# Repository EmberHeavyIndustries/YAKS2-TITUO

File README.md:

# YAKS2 - TITUO

**If you like this project and want to contribute to its further development, please consider donate some $ or € (paypal friends & family, please or DO NOT select "Buying something" from money transfer frontpage).** 

| |||
| ------------------------------ | ---------------------------------------------- | --------------------------- |

**YAKS2-TITUO** is an **"Intelligent" kickstart switcher** for the Amiga A500-A600-A2000 and A1200-A4000, with unique features:

- A500/A600/A2000 version
  - Can switch among four or eight different kickstarts
  - Kickstarts can be flashed at any time by mean of YAKS2 adapter and any common chip flasher, capable of managing 29F080 chips
  - Kickstart selection by mean of CTRL-A-A without the need of any additional wiring inside Amiga
  - Keep track of the selected kickstart upon poweroff
  - Optional audible kickstart selection confirmation 

- A1200/A4000 version
  - Can switch among two or four different kickstarts
  - Kickstarts must be flashed before board assembling (not re-flashable)
  - Kickstart selection by mean of CTRL-A-A without the need of any additional wiring inside Amiga
  - Keep track of the selected kickstart upon poweroff
  - Optional audible kickstart selection confirmation 

## YAKS2-TITUO FLAVORS

The kickswitcher comes in three differen flavors, according to intened use and user preferences:

### **YAKS2-TITUO R02.1**

- Suitable for A500, A600, A2000
- Kickstart images can be flashed at any time (by mean of YAKS2->29F080 adaptor)
- Firmware can be upgraded via ICSP
- Kickstart selection by CTRL-A-A and RST methods (can be easily modded for AUTOSENSE - 1 wire mod)
- Onboard buzzer for audible kickstart switch and named selection evidence
- "D" shaped footprint
- Can switch among 4-kickstart-images or 8-kickstart-images

### **YAKS2-TITUO R03.1al**

- Suitable for A500, A600, A2000
- Kickstart images can be flashed at any time (by mean of YAKS2->29F040 adaptor)
- Firmware cannot be upgraded via ICSP
- Kickstart selection by CTRL-A-A, support both AUTOSENSE (no additional wires) and RST methods
- Can connect an onboard buzzer for audible kickstart switch and named selection evidence
- Visible kickstart switch and named selection evidence
- Small footprint
- Can switch among 4-kickstart-images or 8-kickstart-images

### **YAKS2-TITUO R04.1bl**

- Suitable for A1200 and A4000
- Kickstart images cannot be re-flashed 
- Firmware CAN be upgraded via ICSP
- Kickstart selection by CTRL-A-A, support both AUTOSENSE (no additional wires) and RST methods
- Can connect an external buzzer for audible kickstart switch and named selection evidence
- Visible kickstart switch and named selection evidence
- Small footprint
- Can switch among 2-kickstart-images or 4-kickstart-images

/*************** EDITING IN PROGRESS *************************/

### **EAGLE SCHEMATICS, BOARD LAYOUT and GERBER FILES**

All schemtacis, layouts, gerber files and BOM are in 'Docs' subdirectory

### **FIRMWARE**

Preferred firmware can be downloaded from 'Firmware' subdirectory

## **LICENSE TERMS**

### **Schematics, pcb layouts,  gerbers **
of YAKS2-TITUO are open source, released under the Creative Commons CC BY-NC license.
This means that you are free to:

|                      |                                                                        |
| -------------------- | ---------------------------------------------------------------------- |
|      SHARE           |      copy and redistribute the material in any medium or format        |
|      ADAPT           |      remix, transform, and build upon the material                     |

Under the following terms:

|                       |                                                                        |
| --------------------- | ---------------------------------------------------------------------- |
|     Attribution       | You must give appropriate credit, provide a link to the license, and indicate if changes were made. You may do so in any reasonable manner, but not in any way that suggests the licensor endorses you or your use. |
|      NonCommercial    | You may not use the material for commercial purposes.                  |
|      ShareAlike       | If you remix, transform, or build upon the material, you must distribute your contributions under the same license as the original.          |
| No additional restrict| You may not apply legal terms or technological measures that legally restrict others from doing anything the license permits.  |

### **YAKS2-TITUO FIRMWARE** 
is free to download, copy and redistribuite to be used in conjuction with any YAKS2-TITUO board.
The firmware **CANNOT** be in any way:
- used for any other purpose than YAKS2-TITUO (e.g. flashed in other boards)
- sold, rent or leased. If you were asked to pay for it, you've been tricked

## **Warranty Disclaimer and Limitation of Liability**

YAKS2-TITUO is an hobbyist project without any commercial intention; you understand that we cannot and do not guarantee or warrant neither the YAKS2-TITUO hardware (including but not limited to: schematics, gerbers, pcb, components, assembling, etc.) nor the YAKS2-TITUO software (firmware, etc) from defects, breakage or loss of functionality. You are using HID2AMI under your exclusive risk and responsibility; please understand and AGREE that **WE WILL NOT BE LIABLE FOR ANY LOSS OR DAMAGE CAUSED BY EITHER ANY USE OR ANY MISUSE OF YAKS2-TITUO**

BY MAKING USE OF YAKS2-TITUO, YOU EXPRESSLY AGREE THAT YOUR WILL ACCEPT IT ON "AS IS" BASIS WITHOUT ANY WARRANTIES OF ANY KIND, EITHER EXPRESS OR IMPLIED. YOU ALSO EXPRESSELY AGREE THAT YOUR USE OF HID2AMI HARDWARE AND ITS SOFTWARE COMPONENTS IS AT YOUR OWN RISK. NEITHER THE AUTHOR (Sampedenawa) NOR ANY PERSON ASSOCIATED WITH THE AUTHOR MAKES ANY WARRANTY OR REPRESENTATION WITH RESPECT TO THE COMPLETENESS, SECURITY, RELIABILITY, QUALITY, ACCURACY OR AVAILABILITY OF THE HID2AMI HARDWARE/SOFTWARE.

IF YOU DO NOT UNDERSTAND AND EXPRESSLY AGREE WHAT STATED ABOVE, YOU ARE NOT ENTITLED BY THE AUTHOR TO USE HID2AMI FOR ANY PURPOSE.

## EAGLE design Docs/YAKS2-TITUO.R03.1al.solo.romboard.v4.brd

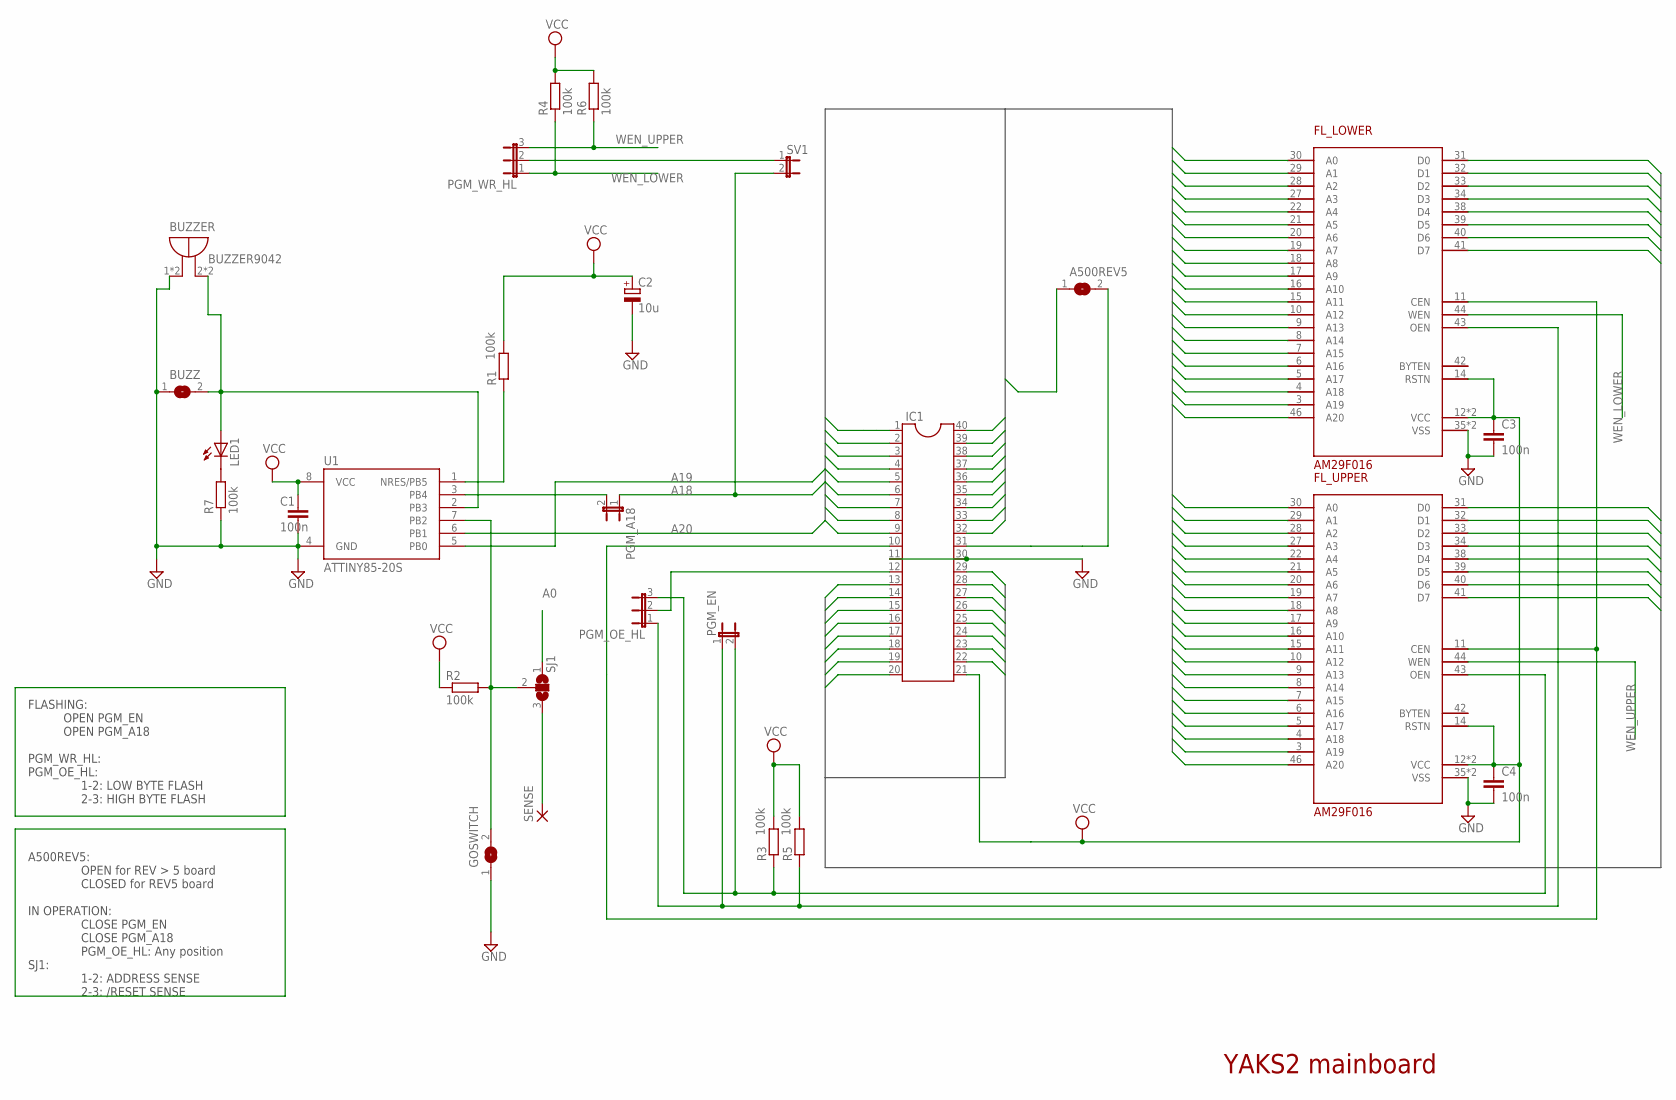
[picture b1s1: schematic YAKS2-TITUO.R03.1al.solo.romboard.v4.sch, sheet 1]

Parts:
A500REV5: SJ
BUZZ: SJ
BUZZER: BUZZER9042; CAPPRD400W65D900H420B
C1, C3, C4: 100n; C0805
C2: 10u; B/3528-21R
FL_LOWER: AM29F016; TSOP48
FL_UPPER: AM29F016; TSOP48
GOSWITCH: SJ
IC1: DIL40
LED1: LEDSML0805; SML0805
PGM_A18: JP1E; JP1
PGM_EN: JP1E; JP1
PGM_OE_HL: JP2E; JP2
PGM_WR_HL: JP2E; JP2
R1, R2, R3, R4, R5, R6, R7: 100k; M0805
SENSE: SMD2; SMD1,27-2,54
SJ1: SJ2W; SJ_2
SV1: JP1E; JP1
U1: ATTINY85-20S; SOIC8_EIAJ_208MIL

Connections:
A0: FL_LOWER.30 (A0), FL_UPPER.30 (A0), IC1.9, SJ1.1
A1: FL_LOWER.29 (A1), FL_UPPER.29 (A1), IC1.8
A2: FL_LOWER.28 (A2), FL_UPPER.28 (A2), IC1.7
A3: FL_LOWER.27 (A3), FL_UPPER.27 (A3), IC1.6
A4: FL_LOWER.22 (A4), FL_UPPER.22 (A4), IC1.5
A5: FL_LOWER.21 (A5), FL_UPPER.21 (A5), IC1.4
A6: FL_LOWER.20 (A6), FL_UPPER.20 (A6), IC1.3
A7: FL_LOWER.19 (A7), FL_UPPER.19 (A7), IC1.2
A8: FL_LOWER.18 (A8), FL_UPPER.18 (A8), IC1.40
A9: FL_LOWER.17 (A9), FL_UPPER.17 (A9), IC1.39
A10: FL_LOWER.16 (A10), FL_UPPER.16 (A10), IC1.38
A11: FL_LOWER.15 (A11), FL_UPPER.15 (A11), IC1.37
A12: FL_LOWER.10 (A12), FL_UPPER.10 (A12), IC1.36
A13: FL_LOWER.9 (A13), FL_UPPER.9 (A13), IC1.35
A14: FL_LOWER.8 (A14), FL_UPPER.8 (A14), IC1.34
A15: FL_LOWER.7 (A15), FL_UPPER.7 (A15), IC1.33
A16: FL_LOWER.6 (A16), FL_UPPER.6 (A16), IC1.32
A17: A500REV5.1, FL_LOWER.5 (A17), FL_UPPER.5 (A17), IC1.1
A18: FL_LOWER.4 (A18), FL_UPPER.4 (A18), PGM_A18.1, SV1.2
A19: FL_LOWER.3 (A19), FL_UPPER.3 (A19), U1.5 (PB0)
A20: FL_LOWER.46 (A20), FL_UPPER.46 (A20), U1.6 (PB1)
BUZZ: BUZZ.2, BUZZER.2 (-), BUZZER.4 (-), LED1.A, U1.2 (PB3)
D0: FL_LOWER.31 (D0), IC1.13
D1: FL_LOWER.32 (D1), IC1.15
D2: FL_LOWER.33 (D2), IC1.17
D3: FL_LOWER.34 (D3), IC1.19
D4: FL_LOWER.38 (D4), IC1.22
D5: FL_LOWER.39 (D5), IC1.24
D6: FL_LOWER.40 (D6), IC1.26
D7: FL_LOWER.41 (D7), IC1.28
D8: FL_UPPER.31 (D0), IC1.14
D9: FL_UPPER.32 (D1), IC1.16
D10: FL_UPPER.33 (D2), IC1.18
D11: FL_UPPER.34 (D3), IC1.20
D12: FL_UPPER.38 (D4), IC1.23
D13: FL_UPPER.39 (D5), IC1.25
D14: FL_UPPER.40 (D6), IC1.27
D15: FL_UPPER.41 (D7), IC1.29
GND: BUZZ.1, BUZZER.1 (+), BUZZER.3 (+), C1.2, C2.-, C3.2, C4.2, FL_LOWER.35 (VSS), FL_LOWER.36 (VSS), FL_UPPER.35 (VSS), FL_UPPER.36 (VSS), GOSWITCH.1, IC1.11, IC1.30, R7.1, U1.4 (GND)
unnamed: LED1.C, R7.2
unnamed: PGM_WR_HL.2, SV1.1
unnamed: A500REV5.2, IC1.31
unnamed: GOSWITCH.2, R2.2, SJ1.2, U1.7 (PB2)
unnamed: IC1.12, PGM_OE_HL.2
unnamed: SENSE.1, SJ1.3
unnamed: R1.1, U1.1 (NRES/PB5)
unnamed: PGM_A18.2, U1.3 (PB4)
OEN_LOWER: FL_LOWER.43 (OEN), PGM_EN.1, PGM_OE_HL.1, R5.1
OEN_UPPER: FL_UPPER.43 (OEN), PGM_EN.2, PGM_OE_HL.3, R3.1
ROM_ENABLE: FL_LOWER.11 (CEN), FL_UPPER.11 (CEN), IC1.10
VCC: C1.1, C2.+, C3.1, C4.1, FL_LOWER.12 (VCC), FL_LOWER.14 (RSTN), FL_LOWER.37 (VCC), FL_UPPER.12 (VCC), FL_UPPER.14 (RSTN), FL_UPPER.37 (VCC), IC1.21, R1.2, R2.1, R3.2, R4.2, R5.2, R6.2, U1.8 (VCC)
WEN_LOWER: FL_LOWER.44 (WEN), PGM_WR_HL.1, R4.1
WEN_UPPER: FL_UPPER.44 (WEN), PGM_WR_HL.3, R6.1

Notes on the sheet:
YAKS2 mainboard
FLASHING: OPEN PGM_EN OPEN PGM_A18 PGM_WR_HL: PGM_OE_HL: 1-2: LOW BYTE FLASH 2-3: HIGH BYTE FLASH
A500REV5: OPEN for REV > 5 board CLOSED for REV5 board IN OPERATION: CLOSE PGM_EN CLOSE PGM_A18 PGM_OE_HL: Any position SJ1: 1-2: ADDRESS SENSE 2-3: /RESET SENSE

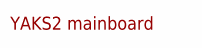
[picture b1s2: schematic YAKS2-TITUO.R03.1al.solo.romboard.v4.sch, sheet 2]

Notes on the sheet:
YAKS2 mainboard

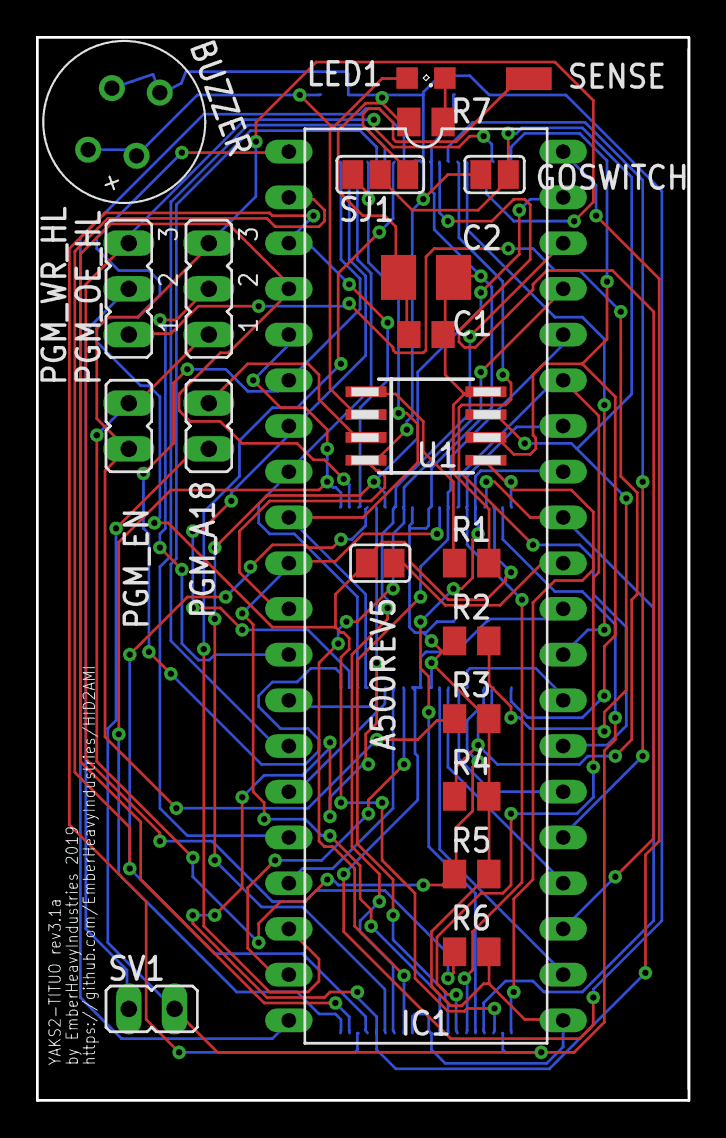
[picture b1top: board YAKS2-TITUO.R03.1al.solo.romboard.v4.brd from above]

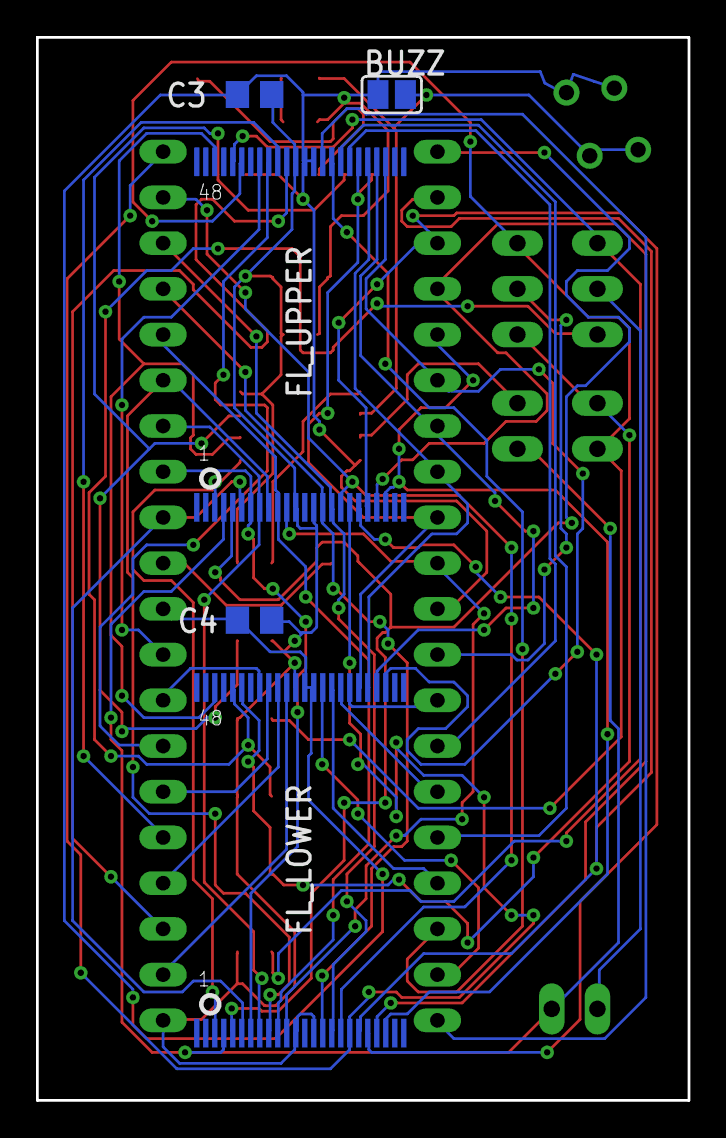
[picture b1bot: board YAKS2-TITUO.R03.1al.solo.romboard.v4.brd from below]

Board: 2 copper layers, 36.2 x 59.1 mm, 27 parts (5 on the bottom side), 53 nets.

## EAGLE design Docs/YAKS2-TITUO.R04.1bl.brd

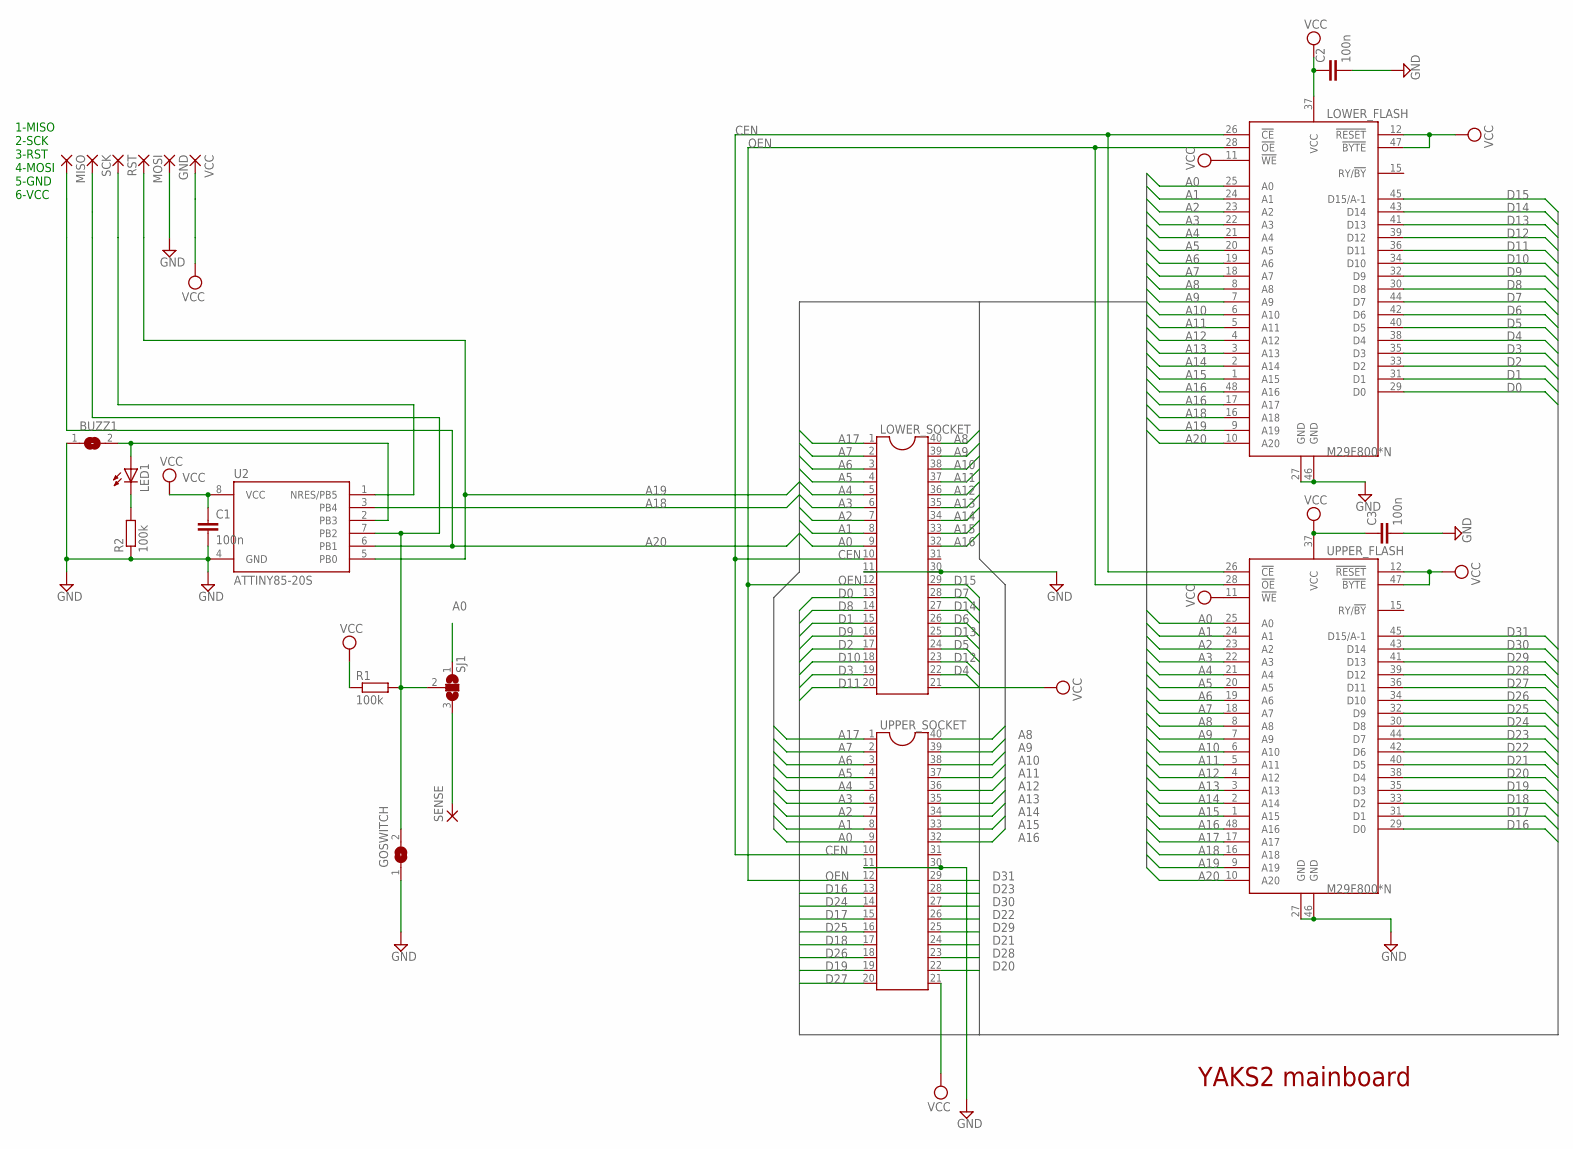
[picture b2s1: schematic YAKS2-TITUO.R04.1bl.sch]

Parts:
BUZZ1: SJ
C1, C2, C3: 100n; C0805
GND: SMD2; SMD1,27-2,54
GOSWITCH: SJ
LED1: LEDSML0805; SML0805
LOWER_FLASH: M29F800*N; 48-TSOP
LOWER_SOCKET: DIL40DIL40SMALLPIN; DIL40SMALLPIN
MISO: SMD2; SMD1,27-2,54
MOSI: SMD2; SMD1,27-2,54
R1, R2: 100k; M0805
RST: SMD2; SMD1,27-2,54
SCK: SMD2; SMD1,27-2,54
SENSE: SMD2; SMD1,27-2,54
SJ1: SJ2W; SJ_2
U2: ATTINY85-20S; SOIC8_EIAJ_208MIL
UPPER_FLASH: M29F800*N; 48-TSOP
UPPER_SOCKET: DIL40DIL40SMALLPIN; DIL40SMALLPIN
VCC: SMD2; SMD1,27-2,54

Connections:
A0: LOWER_FLASH.25 (A0), LOWER_SOCKET.9, SJ1.1, UPPER_FLASH.25 (A0), UPPER_SOCKET.9
A1: LOWER_FLASH.24 (A1), LOWER_SOCKET.8, UPPER_FLASH.24 (A1), UPPER_SOCKET.8
A2: LOWER_FLASH.23 (A2), LOWER_SOCKET.7, UPPER_FLASH.23 (A2), UPPER_SOCKET.7
A3: LOWER_FLASH.22 (A3), LOWER_SOCKET.6, UPPER_FLASH.22 (A3), UPPER_SOCKET.6
A4: LOWER_FLASH.21 (A4), LOWER_SOCKET.5, UPPER_FLASH.21 (A4), UPPER_SOCKET.5
A5: LOWER_FLASH.20 (A5), LOWER_SOCKET.4, UPPER_FLASH.20 (A5), UPPER_SOCKET.4
A6: LOWER_FLASH.19 (A6), LOWER_SOCKET.3, UPPER_FLASH.19 (A6), UPPER_SOCKET.3
A7: LOWER_FLASH.18 (A7), LOWER_SOCKET.2, UPPER_FLASH.18 (A7), UPPER_SOCKET.2
A8: LOWER_FLASH.8 (A8), LOWER_SOCKET.40, UPPER_FLASH.8 (A8), UPPER_SOCKET.40
A9: LOWER_FLASH.7 (A9), LOWER_SOCKET.39, UPPER_FLASH.7 (A9), UPPER_SOCKET.39
A10: LOWER_FLASH.6 (A10), LOWER_SOCKET.38, UPPER_FLASH.6 (A10), UPPER_SOCKET.38
A11: LOWER_FLASH.5 (A11), LOWER_SOCKET.37, UPPER_FLASH.5 (A11), UPPER_SOCKET.37
A12: LOWER_FLASH.4 (A12), LOWER_SOCKET.36, UPPER_FLASH.4 (A12), UPPER_SOCKET.36
A13: LOWER_FLASH.3 (A13), LOWER_SOCKET.35, UPPER_FLASH.3 (A13), UPPER_SOCKET.35
A14: LOWER_FLASH.2 (A14), LOWER_SOCKET.34, UPPER_FLASH.2 (A14), UPPER_SOCKET.34
A15: LOWER_FLASH.1 (A15), LOWER_SOCKET.33, UPPER_FLASH.1 (A15), UPPER_SOCKET.33
A16: LOWER_FLASH.48 (A16), LOWER_SOCKET.32, UPPER_FLASH.48 (A16), UPPER_SOCKET.32
A17: LOWER_FLASH.17 (A17), LOWER_SOCKET.1, UPPER_FLASH.17 (A17), UPPER_SOCKET.1
A18: LOWER_FLASH.16 (A18), U2.3 (PB4), UPPER_FLASH.16 (A18)
A19: LOWER_FLASH.9 (A19), MOSI.1, U2.5 (PB0), UPPER_FLASH.9 (A19)
A20: LOWER_FLASH.10 (A20), MISO.1, U2.6 (PB1), UPPER_FLASH.10 (A20)
BUZZ1: BUZZ1.2, LED1.A, U2.2 (PB3)
CEN: LOWER_FLASH.26 (!CE), LOWER_SOCKET.10, UPPER_FLASH.26 (!CE), UPPER_SOCKET.10
D0: LOWER_FLASH.29 (D0), LOWER_SOCKET.13
D1: LOWER_FLASH.31 (D1), LOWER_SOCKET.15
D2: LOWER_FLASH.33 (D2), LOWER_SOCKET.17
D3: LOWER_FLASH.35 (D3), LOWER_SOCKET.19
D4: LOWER_FLASH.38 (D4), LOWER_SOCKET.22
D5: LOWER_FLASH.40 (D5), LOWER_SOCKET.24
D6: LOWER_FLASH.42 (D6), LOWER_SOCKET.26
D7: LOWER_FLASH.44 (D7), LOWER_SOCKET.28
D8: LOWER_FLASH.30 (D8), LOWER_SOCKET.14
D9: LOWER_FLASH.32 (D9), LOWER_SOCKET.16
D10: LOWER_FLASH.34 (D10), LOWER_SOCKET.18
D11: LOWER_FLASH.36 (D11), LOWER_SOCKET.20
D12: LOWER_FLASH.39 (D12), LOWER_SOCKET.23
D13: LOWER_FLASH.41 (D13), LOWER_SOCKET.25
D14: LOWER_FLASH.43 (D14), LOWER_SOCKET.27
D15: LOWER_FLASH.45 (D15/A-1), LOWER_SOCKET.29
D16: UPPER_FLASH.29 (D0), UPPER_SOCKET.13
D17: UPPER_FLASH.31 (D1), UPPER_SOCKET.15
D18: UPPER_FLASH.33 (D2), UPPER_SOCKET.17
D19: UPPER_FLASH.35 (D3), UPPER_SOCKET.19
D20: UPPER_FLASH.38 (D4), UPPER_SOCKET.22
D21: UPPER_FLASH.40 (D5), UPPER_SOCKET.24
D22: UPPER_FLASH.42 (D6), UPPER_SOCKET.26
D23: UPPER_FLASH.44 (D7), UPPER_SOCKET.28
D24: UPPER_FLASH.30 (D8), UPPER_SOCKET.14
D25: UPPER_FLASH.32 (D9), UPPER_SOCKET.16
D26: UPPER_FLASH.34 (D10), UPPER_SOCKET.18
D27: UPPER_FLASH.36 (D11), UPPER_SOCKET.20
D28: UPPER_FLASH.39 (D12), UPPER_SOCKET.23
D29: UPPER_FLASH.41 (D13), UPPER_SOCKET.25
D30: UPPER_FLASH.43 (D14), UPPER_SOCKET.27
D31: UPPER_FLASH.45 (D15/A-1), UPPER_SOCKET.29
GND: BUZZ1.1, C1.2, C2.2, C3.2, GND.1, GOSWITCH.1, LOWER_FLASH.27 (GND), LOWER_FLASH.46 (GND), LOWER_SOCKET.11, LOWER_SOCKET.30, R2.1, U2.4 (GND), UPPER_FLASH.27 (GND), UPPER_FLASH.46 (GND), UPPER_SOCKET.11, UPPER_SOCKET.30
unnamed: LED1.C, R2.2
unnamed: RST.1, U2.1 (NRES/PB5)
unnamed: SENSE.1, SJ1.3
OEN: LOWER_FLASH.28 (!OE), LOWER_SOCKET.12, UPPER_FLASH.28 (!OE), UPPER_SOCKET.12
SCK/PB2: GOSWITCH.2, R1.2, SCK.1, SJ1.2, U2.7 (PB2)
VCC: C1.1, C2.1, C3.1, LOWER_FLASH.11 (!WE), LOWER_FLASH.12 (!RESET), LOWER_FLASH.37 (VCC), LOWER_FLASH.47 (!BYTE), LOWER_SOCKET.21, R1.1, U2.8 (VCC), UPPER_FLASH.11 (!WE), UPPER_FLASH.12 (!RESET), UPPER_FLASH.37 (VCC), UPPER_FLASH.47 (!BYTE), UPPER_SOCKET.21, VCC.1

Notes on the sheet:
YAKS2 mainboard
1-MISO 2-SCK 3-RST 4-MOSI 5-GND 6-VCC

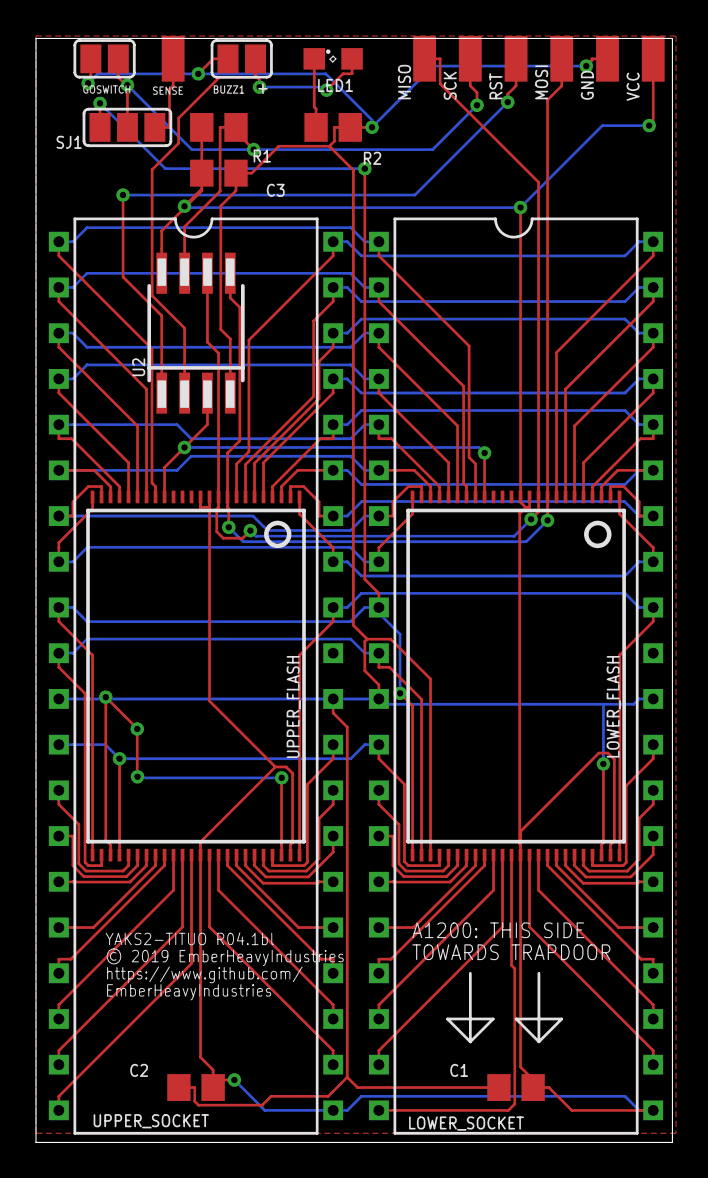
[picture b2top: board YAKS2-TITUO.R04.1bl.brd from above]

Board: 2 copper layers, 35.4 x 61.3 mm, 21 parts (0 on the bottom side), 62 nets.

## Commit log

2019-05-31 Create firmware
2019-05-31 Create x
2025-11-12 Remove

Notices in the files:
README.md:
LICENSE TERMS:
[License: CC BY-NC-SA 4.0](https://creativecommons.org/licenses/by-nc-sa/4.0/)
Docs/YAKS2-TITUO.R04.1bl.brd:
© 2019 EmberHeavyIndustries
